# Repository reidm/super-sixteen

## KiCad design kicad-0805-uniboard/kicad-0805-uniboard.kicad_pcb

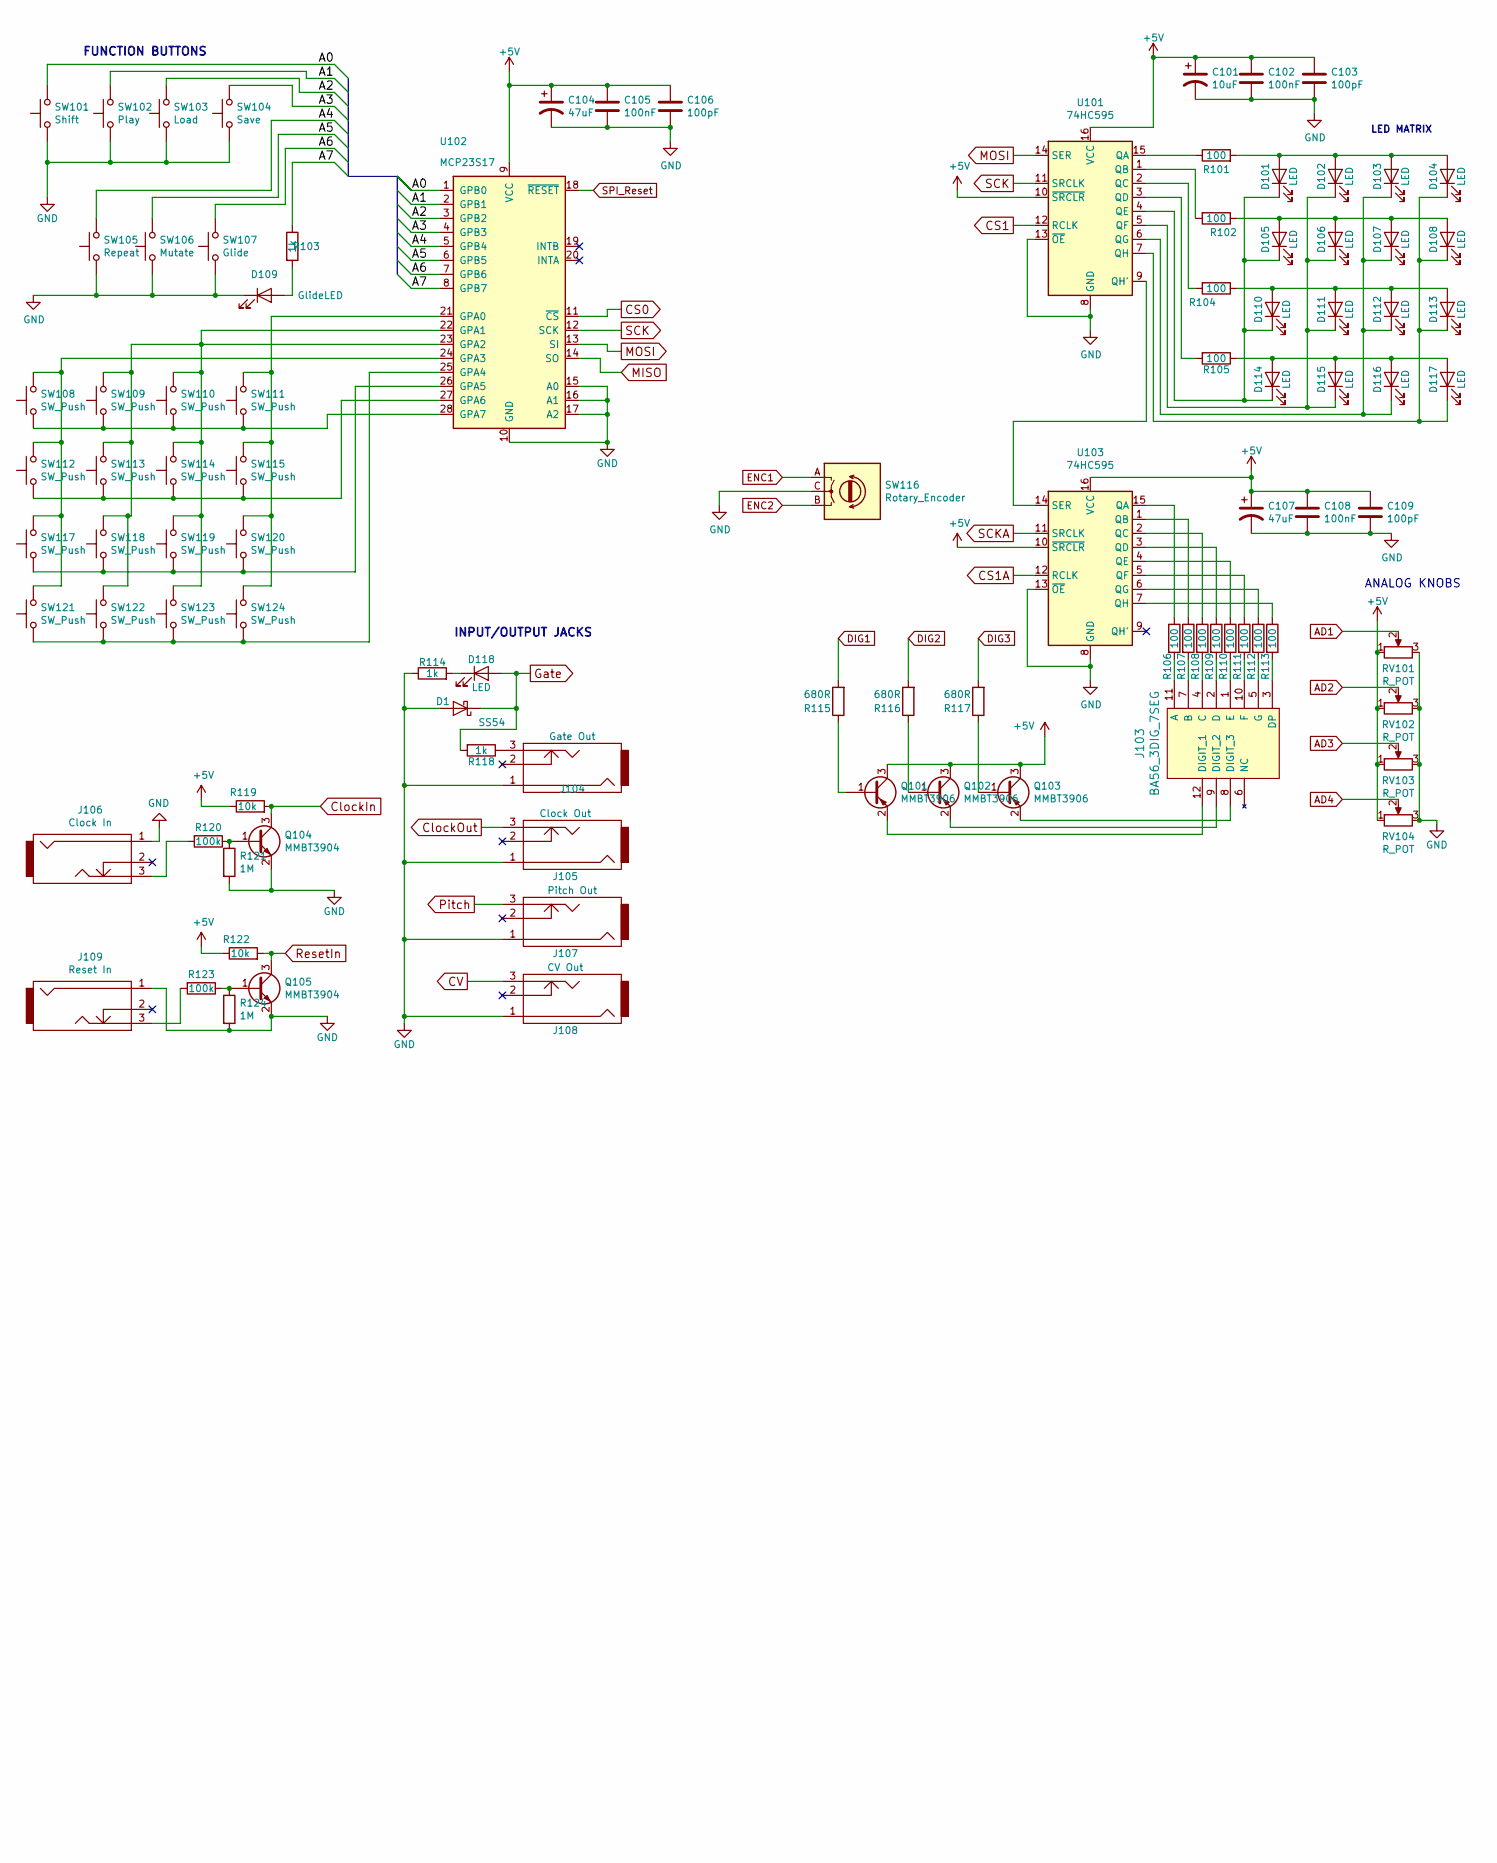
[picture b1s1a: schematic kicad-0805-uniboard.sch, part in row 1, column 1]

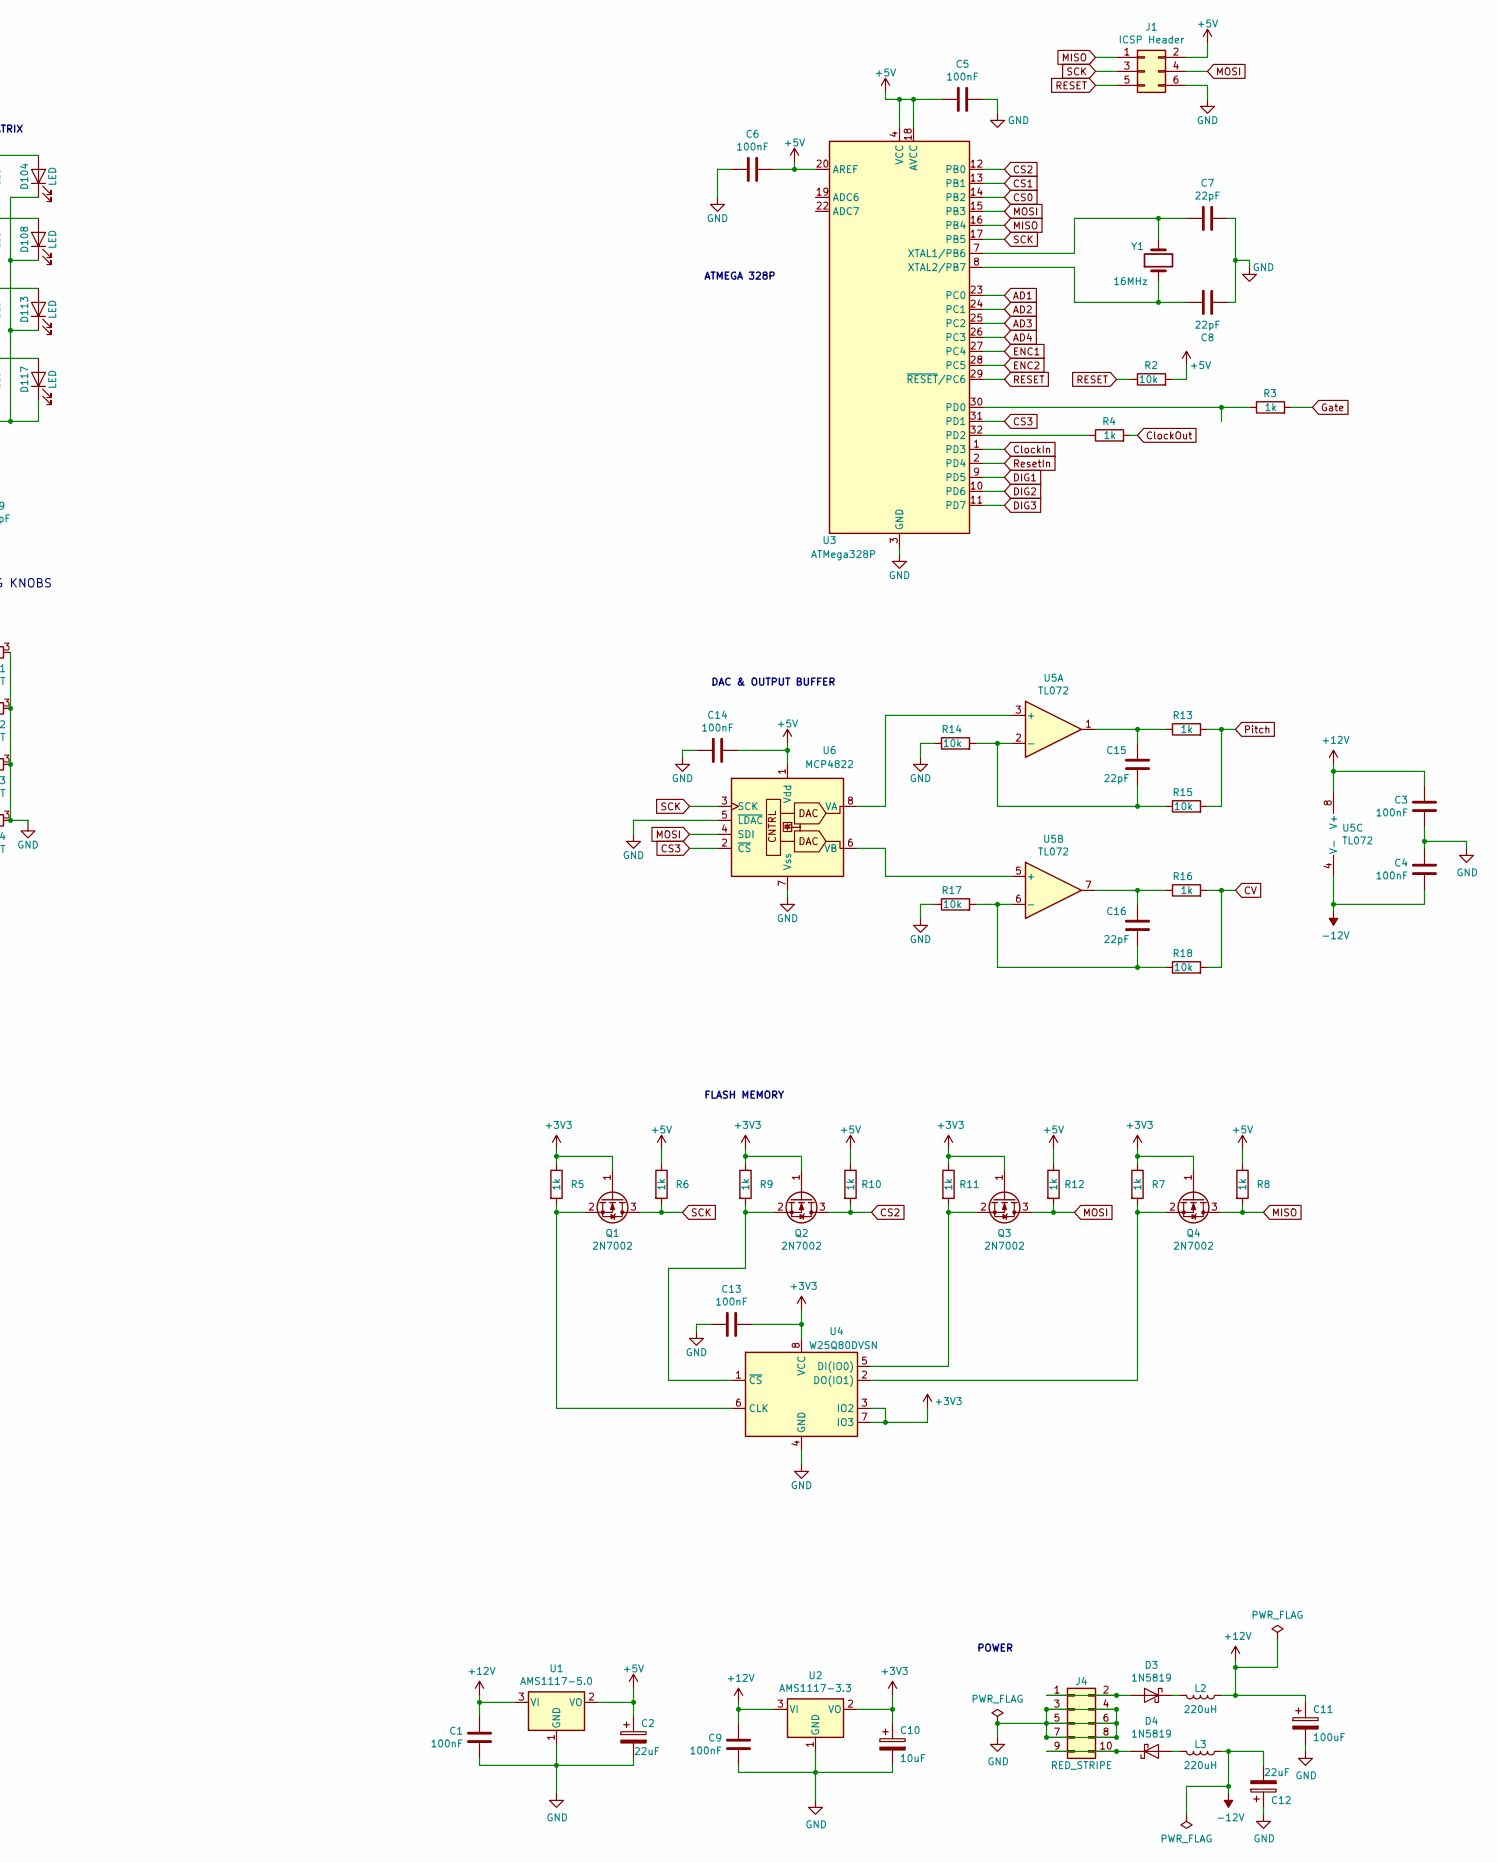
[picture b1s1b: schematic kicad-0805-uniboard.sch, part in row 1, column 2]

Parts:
C1, C3, C4, C5, C6, C9, C13, C14: 100nF; C_0805_2012Metric_Pad1.15x1.40mm_HandSolder
C2, C12: 22uF; CP_Elec_5x5.7
C7, C8, C15, C16: 22pF; C_0805_2012Metric_Pad1.15x1.40mm_HandSolder
C10: 10uF; CP_Elec_5x5.7
C11: 100uF; CP_Elec_6.3x7.7
C101: 10uF; CP_Elec_6.3x7.7; MFG Part Number VES470M1HTR-0607; LCSC Part Number C108053
C102, C105, C108: 100nF; C_0805_2012Metric_Pad1.15x1.40mm_HandSolder; MFG Part Number CC0603KRX7R9BB104; LCSC Part Number C14663
C103, C106, C109: 100pF; C_0805_2012Metric_Pad1.15x1.40mm_HandSolder; MFG Part Number CL10C101JB8NNNC; LCSC Part Number C14858
C104, C107: 47uF; CP_Elec_5x5.7; MFG Part Number VES470M1HTR-0607; LCSC Part Number C108053
D1: SS54; D_SMA_Handsoldering; MFG Part Number SS54; LCSC Part Number C22452
D3, D4: 1N5819; D_0805_2012Metric_Pad1.15x1.40mm_HandSolder
D101, D102, D103, D104, D105, D106, D107, D108, D110, D111, D112, D113, D114, D115, D116, D117, D118: LED; LED_D3.0mm
D109: GlideLED; LED_D3.0mm
J1: ICSP Header; PinHeader_2x03_P2.54mm_Vertical
J4: RED_STRIPE; PinHeader_2x05_P2.54mm_Vertical
J103: BA56_3DIG_7SEG
J104: Gate Out; PJ301M-12
J105: Clock Out; PJ301M-12
J106: Clock In; PJ301M-12
J107: Pitch Out; PJ301M-12
J108: CV Out; PJ301M-12
J109: Reset In; PJ301M-12
L2, L3: 220uH; L_1210_3225Metric_Pad1.42x2.65mm_HandSolder
Q1, Q2, Q3, Q4: 2N7002; SOT-23
Q101, Q102, Q103: MMBT3906; SOT-23_Handsoldering; MFG Part Number MMBT3906LT1G; LCSC Part Number C53444
Q104, Q105: MMBT3904; SOT-23_Handsoldering; MFG Part Number MMBT3904; LCSC Part Number C20526
R2, R14, R15, R17, R18, R119, R122: 10k; R_0805_2012Metric_Pad1.15x1.40mm_HandSolder; MFG Part Number 0603WAF1002T5E; LCSC Part Number C25804
R3, R4, R13, R16: 1k; R_0805_2012Metric_Pad1.15x1.40mm_HandSolder; MFG Part Number 0603WAF1002T5E; LCSC Part Number C25804
R5, R6, R7, R8, R9, R10, R11, R12: 1k; R_0805_2012Metric_Pad1.15x1.40mm_HandSolder; MFG Part Number 0603WAF1000T5E; LCSC Part Number C22775
R101, R102, R104, R105, R106, R107, R108, R109, R110, R111, R112, R113: 100; R_0805_2012Metric_Pad1.15x1.40mm_HandSolder; MFG Part Number 0603WAF1000T5E; LCSC Part Number C22775
R103, R114, R118: 1k; R_0805_2012Metric_Pad1.15x1.40mm_HandSolder; MFG Part Number 0603WAF1001T5E; LCSC Part Number C21190
R115, R116, R117: 680R; R_0805_2012Metric_Pad1.15x1.40mm_HandSolder; MFG Part Number 0603WAF6800T5E; LCSC Part Number C23228
R120, R123: 100k; R_0805_2012Metric_Pad1.15x1.40mm_HandSolder; MFG Part Number 0603WAF1003T5E; LCSC Part Number C25803
R121, R124: 1M; R_0805_2012Metric_Pad1.15x1.40mm_HandSolder; MFG Part Number 0603WAF1004T5E; LCSC Part Number C22935
RV101, RV102, RV103, RV104: R_POT; Alpha9mmPot-SemiSMD4
SW101: Shift; SW_PUSH_6mm
SW102: Play; SW_PUSH_6mm
SW103: Load; SW_PUSH_6mm
SW104: Save; SW_PUSH_6mm
SW105: Repeat; Push_E-Switch_KS01Q01
SW106: Mutate; Push_E-Switch_KS01Q01
SW107: Glide; SW_PUSH_6mm
SW108, SW109, SW110, SW111, SW112, SW113, SW114, SW115, SW117, SW118, SW119, SW120, SW121, SW122, SW123, SW124: SW_Push; SW_PUSH_6mm
SW116: Rotary_Encoder; RotaryEncoder_Alps_EC12E_Vertical_H20mm
U1: AMS1117-5.0; SOT-223-3_TabPin2
U2: AMS1117-3.3; SOT-223-3_TabPin2
U3: ATMega328P; TQFP-32_7x7mm_P0.8mm
U4: W25Q80DVSN; SOIC-8_5.23x5.23mm_P1.27mm
U5: TL072; SOIC-8_3.9x4.9mm_P1.27mm
U6: MCP4822; SOIC-8_3.9x4.9mm_P1.27mm
U101, U103: 74HC595; SOIC-16_3.9x9.9mm_Pitch1.27mm; MFG Part Number 74HC595D,118; LCSC Part Number C5947
U102: MCP23S17; SOIC-28W_7.5x18.7mm_P1.27mm
Y1: 16MHz; Crystal_HC49-4H_Vertical

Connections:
+3V3: C10.1, C13.2, Q1.1 (G), Q2.1 (G), Q3.1 (G), Q4.1 (G), R5.1, R7.1, R9.1, R11.1, U2.2 (VO), U4.3 (IO2), U4.7 (IO3), U4.8 (VCC)
+5V: C2.1, C5.2, C6.2, C14.2, C101.1, C102.1, C103.1, C104.1, C105.1, C106.1, C107.1, C108.1, C109.1, J1.2, Q101.3 (C), Q102.3 (C), Q103.3 (C), R2.2, R6.1, R8.1, R10.1, R12.1, R119.1, R122.1, RV101.1, RV102.1, RV103.1, RV104.1, U1.2 (VO), U3.4 (VCC), U3.6 (VCC), U3.18 (AVCC), U3.20 (AREF), U6.1 (Vdd), U101.10 (~SRCLR), U101.16 (VCC), U102.9 (VCC), U103.10 (~SRCLR), U103.16 (VCC)
+12V: C1.2, C3.2, C9.2, C11.1, L2.1, U1.3 (VI), U2.3 (VI), U5.8 (V+)
-12V: C4.1, C12.2, L3.1, U5.4 (V-)
/A0: SW101.2, U102.1 (GPB0)
/A1: SW102.2, U102.2 (GPB1)
/A2: SW103.2, U102.3 (GPB2)
/A3: SW104.2, U102.4 (GPB3)
/A4: SW105.2, U102.5 (GPB4)
/A5: SW106.2, U102.6 (GPB5)
/A6: SW107.2, U102.7 (GPB6)
/A7: R103.1, U102.8 (GPB7)
AD1: RV101.2, U3.23 (PC0)
AD2: RV102.2, U3.24 (PC1)
AD3: RV103.2, U3.25 (PC2)
AD4: RV104.2, U3.26 (PC3)
CS0: U3.14 (PB2), U102.11 (~CS)
CS1: U3.13 (PB1), U101.12 (RCLK)
CS1A: U103.12 (RCLK)
CS2: Q2.3 (D), R10.2, U3.12 (PB0)
CS3: U3.31 (PD1), U6.2 (~CS)
CV: J108.3, R16.2, R18.2
ClockIn: Q104.3 (C), R119.2, U3.1 (PD3)
ClockOut: J105.3, R4.2
DIG1: R115.2, U3.9 (PD5)
DIG2: R116.2, U3.10 (PD6)
DIG3: R117.2, U3.11 (PD7)
ENC1: SW116.A, U3.27 (PC4)
ENC2: SW116.B, U3.28 (PC5)
GND: C1.1, C2.2, C3.1, C4.2, C5.1, C6.1, C7.1, C8.2, C9.1, C10.2, C11.2, C12.1, C13.1, C14.1, C101.2, C102.2, C103.2, C104.2, C105.2, C106.2, C107.2, C108.2, C109.2, D1.2 (A), D109.1 (K), J1.6, J4.3, J4.4, J4.5, J4.6, J4.7, J4.8, J104.1, J105.1, J106.1, J107.1, J108.1, J109.1, Q104.2 (E), Q105.2 (E), R14.1, R17.1, R114.1, R121.2, R124.2, RV101.3, RV102.3, RV103.3, RV104.3, SW101.1, SW102.1, SW103.1, SW104.1, SW105.1, SW106.1, SW107.1, SW116.C, U1.1 (GND), U2.1 (GND), U3.3 (GND), U3.5 (GND), U3.21 (GND), U4.4 (GND), U6.5 (~LDAC), U6.7 (Vss), U101.8 (GND), U101.13 (~OE), U102.10 (GND), U102.15 (A0), U102.16 (A1), U102.17 (A2), U103.8 (GND), U103.13 (~OE)
Gate: D1.1 (K), D118.2 (A), R3.2, R118.2
MISO: J1.1, Q4.3 (D), R8.2, U3.16 (PB4), U102.14 (SO)
MOSI: J1.4, Q3.3 (D), R12.2, U3.15 (PB3), U6.4 (SDI), U101.14 (SER), U102.13 (SI)
unnamed: C7.2, U3.7 (XTAL1/PB6), Y1.2
unnamed: C8.1, U3.8 (XTAL2/PB7), Y1.1
unnamed: C15.1, R13.1, U5.1
unnamed: C15.2, R14.2, R15.1, U5.2 (-)
unnamed: C16.1, R16.1, U5.7
unnamed: C16.2, R17.2, R18.1, U5.6 (-)
unnamed: D3.1 (K), L2.2
unnamed: D3.2 (A), J4.1, J4.2
unnamed: D4.1 (K), J4.9, J4.10
unnamed: D4.2 (A), L3.2
unnamed: D101.1 (K), D105.1 (K), D110.1 (K), D114.1 (K), U101.4 (QE)
unnamed: D101.2 (A), D102.2 (A), D103.2 (A), D104.2 (A), R101.2
unnamed: D102.1 (K), D106.1 (K), D111.1 (K), D115.1 (K), U101.5 (QF)
unnamed: D103.1 (K), D107.1 (K), D112.1 (K), D116.1 (K), U101.6 (QG)
unnamed: D104.1 (K), D108.1 (K), D113.1 (K), D117.1 (K), U101.7 (QH)
unnamed: D105.2 (A), D106.2 (A), D107.2 (A), D108.2 (A), R102.1
unnamed: D109.2 (A), R103.2
unnamed: D110.2 (A), D111.2 (A), D112.2 (A), D113.2 (A), R104.1
unnamed: D114.2 (A), D115.2 (A), D116.2 (A), D117.2 (A), R105.1
unnamed: D118.1 (K), R114.2
unnamed: J103.1 (E), R110.2
unnamed: J103.2 (D), R109.2
unnamed: J103.3 (DP), R113.2
unnamed: J103.4 (C), R108.2
unnamed: J103.5 (G), R112.2
unnamed: J103.7 (B), R107.2
unnamed: J103.8 (DIGIT_3), Q103.2 (E)
unnamed: J103.9 (DIGIT_2), Q102.2 (E)
unnamed: J103.10 (F), R111.2
unnamed: J103.11 (A), R106.2
unnamed: J103.12 (DIGIT_1), Q101.2 (E)
unnamed: J104.3, R118.1
unnamed: J106.3, R120.2
unnamed: J109.3, R123.2
unnamed: Q1.2 (S), R5.2, U4.6 (CLK)
unnamed: Q2.2 (S), R9.2, U4.1 (~CS)
unnamed: Q3.2 (S), R11.2, U4.5 (DI(IO0))
unnamed: Q4.2 (S), R7.2, U4.2 (DO(IO1))
unnamed: Q101.1 (B), R115.1
unnamed: Q102.1 (B), R116.1
unnamed: Q103.1 (B), R117.1
unnamed: Q104.1 (B), R120.1, R121.1
unnamed: Q105.1 (B), R123.1, R124.1
unnamed: R3.1, U3.30 (PD0)
unnamed: R4.1, U3.32 (PD2)
unnamed: R101.1, U101.15 (QA)
unnamed: R102.2, U101.1 (QB)
unnamed: R104.2, U101.2 (QC)
unnamed: R105.2, U101.3 (QD)
unnamed: R106.1, U103.15 (QA)
unnamed: R107.1, U103.1 (QB)
unnamed: R108.1, U103.2 (QC)
unnamed: R109.1, U103.3 (QD)
unnamed: R110.1, U103.4 (QE)
unnamed: R111.1, U103.5 (QF)
unnamed: R112.1, U103.6 (QG)
unnamed: R113.1, U103.7 (QH)
unnamed: SW108.1, SW109.1, SW110.1, SW111.1, U102.28 (GPA7)
unnamed: SW108.2, SW112.2, SW117.2, SW121.2, U102.24 (GPA3)
unnamed: SW109.2, SW110.2, SW113.2, SW114.2, SW118.2, SW119.2, SW122.2, SW123.2, U102.22 (GPA1), U102.23 (GPA2)
unnamed: SW111.2, SW115.2, SW120.2, SW124.2, U102.21 (GPA0)
unnamed: SW112.1, SW113.1, SW114.1, SW115.1, U102.27 (GPA6)
unnamed: SW117.1, SW118.1, SW119.1, SW120.1, U102.26 (GPA5)
unnamed: SW121.1, SW122.1, SW123.1, SW124.1, U102.25 (GPA4)
unnamed: U5.3 (+), U6.8 (VA)
unnamed: U5.5 (+), U6.6 (VB)
unnamed: U101.9 (QH'), U103.14 (SER)
Pitch: J107.3, R13.2, R15.2
RESET: J1.5, R2.1, U3.29 (~RESET~/PC6)
ResetIn: Q105.3 (C), R122.2, U3.2 (PD4)
SCK: J1.3, Q1.3 (D), R6.2, U3.17 (PB5), U6.3 (SCK), U101.11 (SRCLK), U102.12 (SCK)
SCKA: U103.11 (SRCLK)
SPI_Reset: U102.18 (~RESET)

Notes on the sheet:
ANALOG KNOBS
FUNCTION BUTTONS
INPUT/OUTPUT JACKS
LED MATRIX
ATMEGA 328P
POWER
DAC & OUTPUT BUFFER
FLASH MEMORY

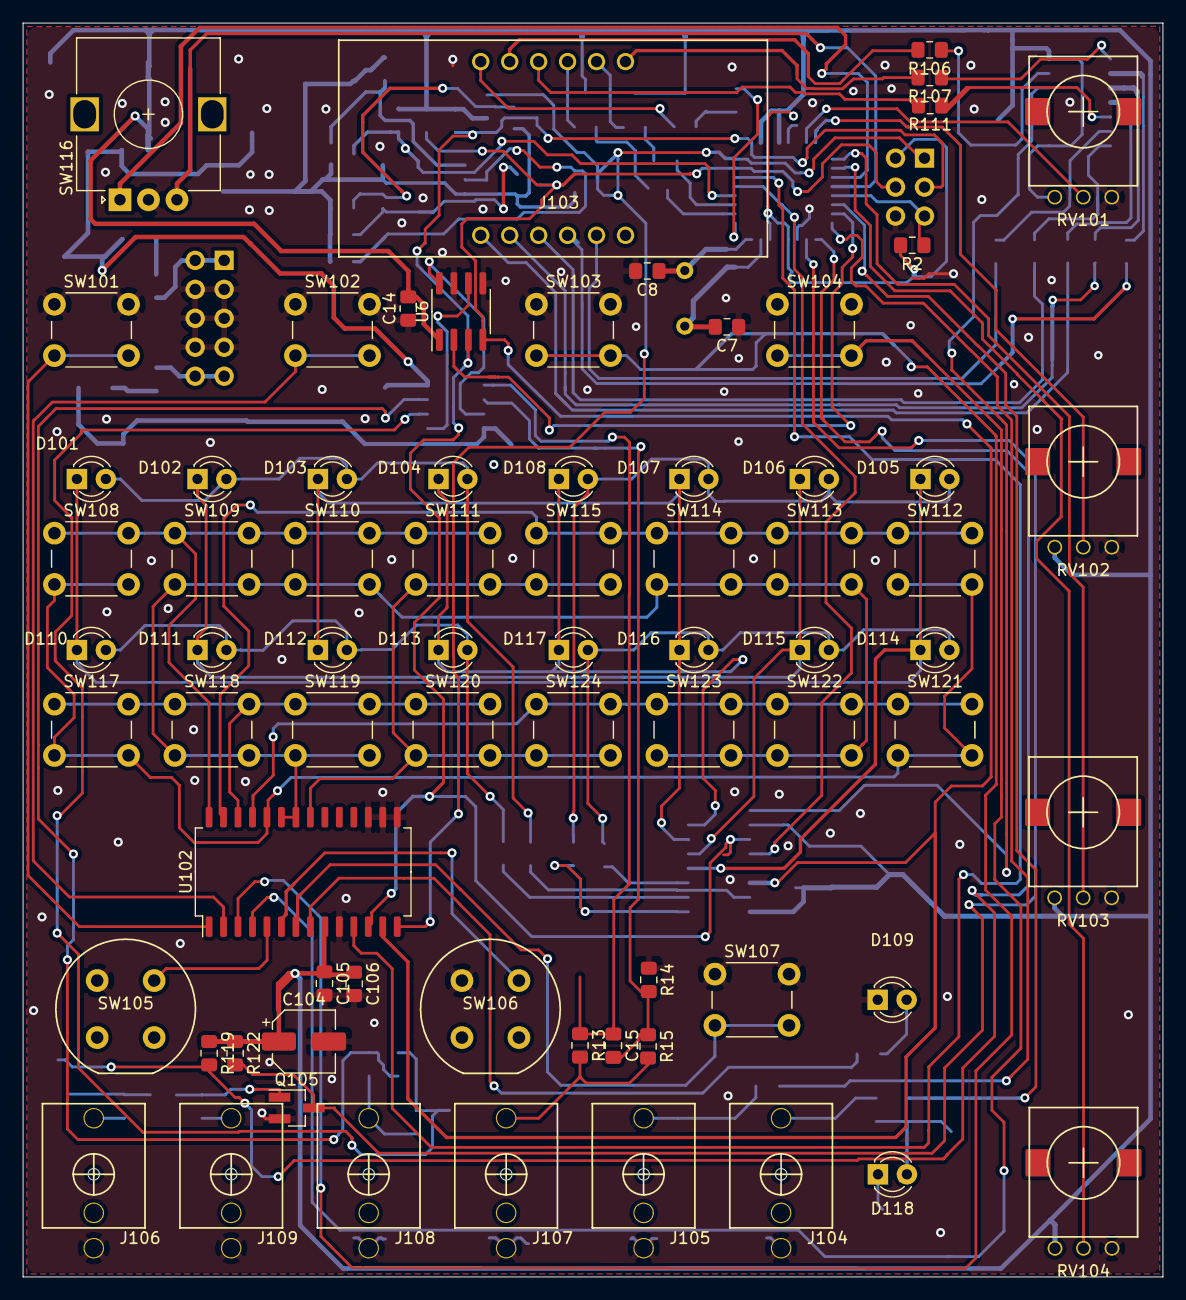
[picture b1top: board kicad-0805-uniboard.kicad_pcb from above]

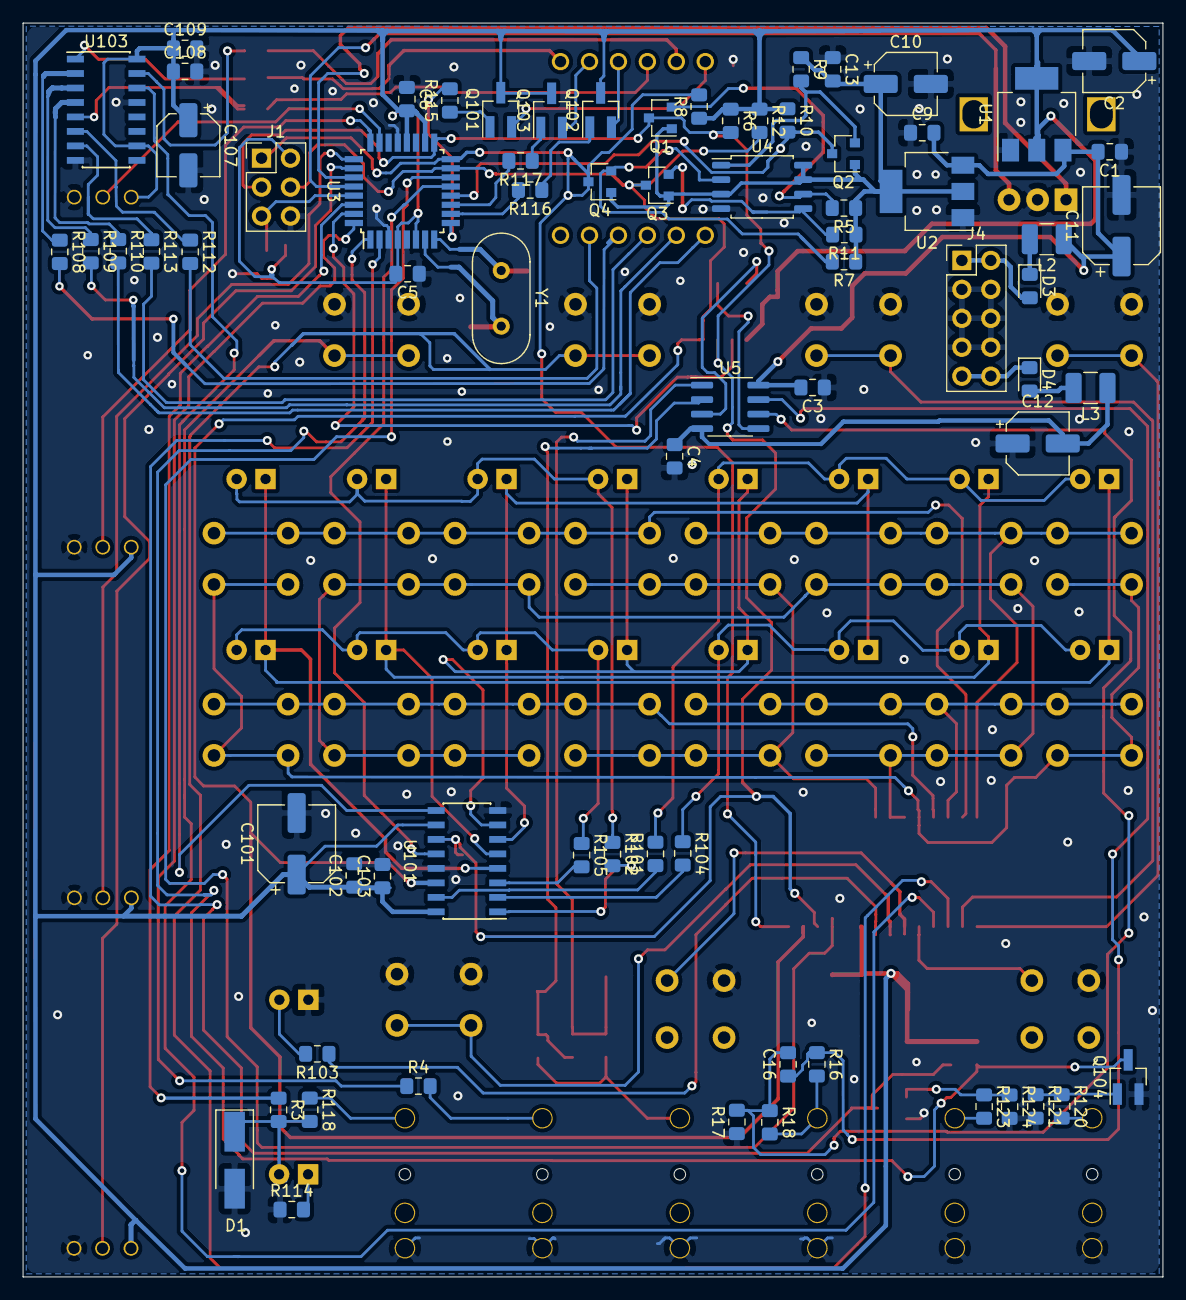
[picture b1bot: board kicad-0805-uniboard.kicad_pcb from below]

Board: 2 copper layers, 100.0 x 110.0 mm, 145 parts (73 on the bottom side), 103 nets.

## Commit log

2020-06-18 Initial circuit ported from second board.
2020-06-18 Initial fp's changed. Cleared old routings.
2020-06-19 Forgot some schematic stuff. More placement.
2020-06-19 More placement work.
2020-06-19 Prepped to throw more stuff on there..
2020-06-19 Initial placement complete.
2020-06-19 More routes.
2020-06-20 More routing. This will be tightgit status .
2020-06-20 It won't work this way!
2020-06-20 Getting there.
2020-06-20 More dots connected.
2020-06-20 More routing added. The top third of the board is filled in.
2020-06-21 More routes added.
2020-06-26 Initial routing complete.
2020-06-26 Improved ground planes.
